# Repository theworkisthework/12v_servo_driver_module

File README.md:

12v (to 5v) Servo driver module

Allows connecting a standard 5v servo directly to a 12v supply.
Intended for the plotter controller board and avoids having to change the supply voltage jumper on the main board.

The thinking is if we standardize on 12v that will allow more scope for different tool heads.

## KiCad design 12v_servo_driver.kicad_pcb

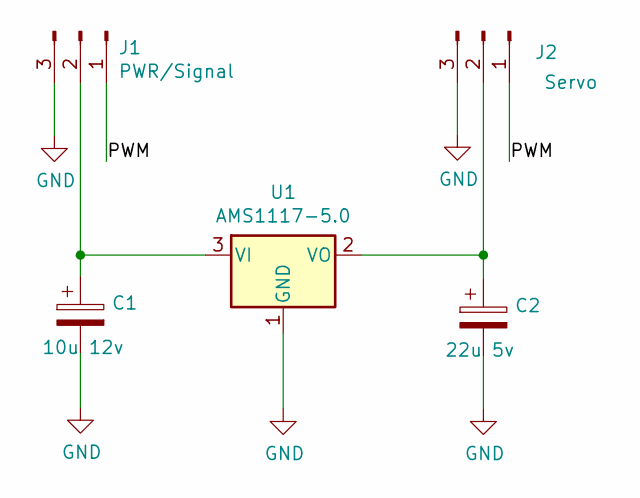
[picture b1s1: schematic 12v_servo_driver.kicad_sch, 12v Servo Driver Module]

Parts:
C1: 10u 12v; CP_EIA-3528-21_Kemet-B; LCSC C117028
C2: 22u 5v; CP_EIA-3528-21_Kemet-B; LCSC C2798070
J1: PWR/Signal; JST_PH_S3B-PH-K_1x03_P2.00mm_Horizontal; LCSC C146083
J2: Servo; PinHeader_1x03_P2.54mm_Horizontal; LCSC C8886
U1: AMS1117-5.0; SOT-223; LCSC C347223

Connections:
/PWM: J1.1, J2.1
GND: C1.2, C2.2, J1.3, J2.3, U1.1 (GND)
unnamed: C1.1, J1.2, U1.3 (VI)
unnamed: C2.1, J2.2, U1.2 (VO)

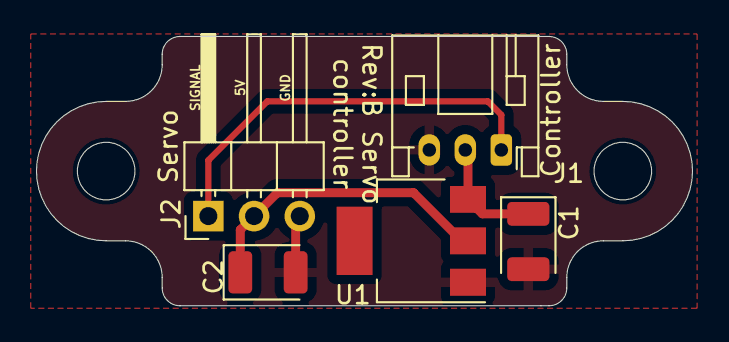
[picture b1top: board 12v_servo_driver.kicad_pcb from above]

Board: 2 copper layers, 36.4 x 15.0 mm, 5 parts (0 on the bottom side), 4 nets.

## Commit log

2022-09-19 Update page info and add gerber
2023-03-03 Add pinout documentation
2023-03-06 Add step model
2023-03-06 Update project for kicad 7 and add doc
2023-03-07 RevB
    Right angle connectors on both servo and controller connectors.
    Both connectors on same side of the board.
2023-03-07 Make power tracks 0.75mm rather than 0.5mm
2023-03-10 Update gerber for RevB
2023-03-18 Update images for RevB
2023-03-18 Update board version in pinmap
2023-03-24 Update pin map to correctly show individual pins
2023-03-25 Fix pinmap
